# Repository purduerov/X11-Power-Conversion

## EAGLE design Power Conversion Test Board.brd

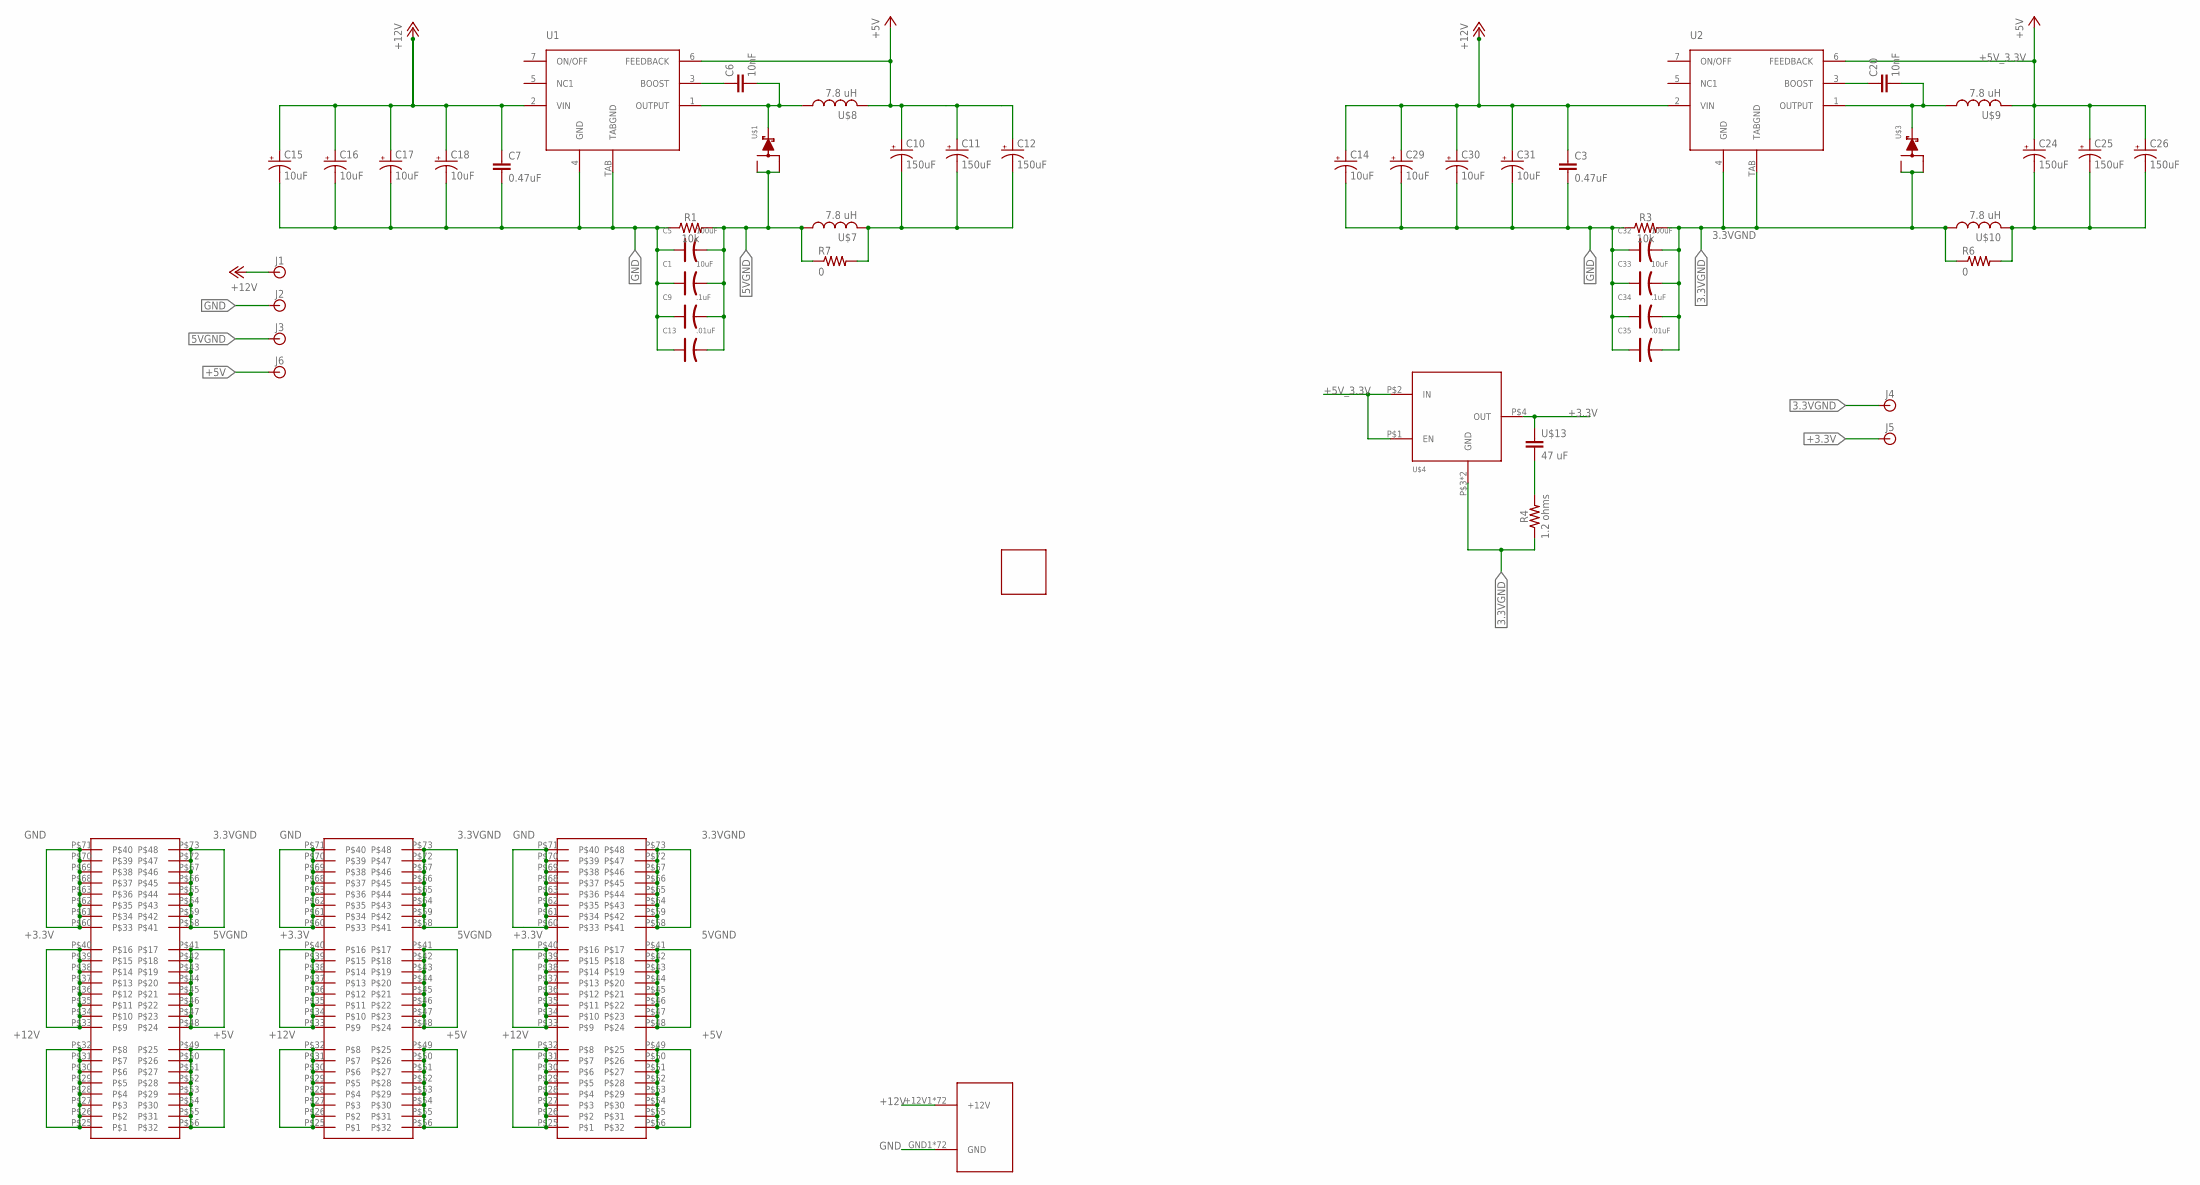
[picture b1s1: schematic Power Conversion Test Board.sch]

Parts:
C1, C33: 10uF; AVX-A
C3, C7: 0.47uF; C0603
C5, C32: 100uF; AVX-A
C6, C20: 10nF; 0603
C9, C34: .1uF; AVX-A
C10, C11, C12, C24, C25, C26: 150uF; CTAN(7.30_4.30MM)
C13, C35: .01uF; AVX-A
C14, C15, C16, C17, C18, C29, C30, C31: 10uF; CTAN(7.30_4.30MM)
J1, J2, J3, J4, J5, J6: BANANA_CONN
R1, R3: 10k; 0603
R4: 1.2 ohms; 0603
R6, R7: 0; R1206
U1, U2: LM2678
U$1, U$3: SWITCHMODE_SCHOTTKY; DPAK-3
U$2: PDB_PCB_CONNEC; PDB_PCB_2
U$4: TO-263
U$5: BOARDPCB; PCB
U$6, U$11, U$12: ET60S
U$7, U$8, U$9, U$10: 7.8 uH; HCMA1305
U$13: 47 uF; RESC0603_N

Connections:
3.3VGND: C32.-, C33.-, C34.-, C35.-, J4.P$1, R3.2, R4.1, R6.1, U2.4 (GND), U2.TAB (TABGND), U$3.P$1, U$3.P$3, U$4.P$3 (GND), U$4.P$6 (GND), U$6.P$58, U$6.P$59, U$6.P$64, U$6.P$65, U$6.P$66, U$6.P$67, U$6.P$72, U$6.P$73, U$10.P$1 (1), U$11.P$58, U$11.P$59, U$11.P$64, U$11.P$65, U$11.P$66, U$11.P$67, U$11.P$72, U$11.P$73, U$12.P$58, U$12.P$59, U$12.P$64, U$12.P$65, U$12.P$66, U$12.P$67, U$12.P$72, U$12.P$73
5VGND: C1.-, C5.-, C9.-, C13.-, J3.P$1, R1.2, R7.1, U$1.P$1, U$1.P$3, U$6.P$41, U$6.P$42, U$6.P$43, U$6.P$44, U$6.P$45, U$6.P$46, U$6.P$47, U$6.P$48, U$7.P$1 (1), U$11.P$41, U$11.P$42, U$11.P$43, U$11.P$44, U$11.P$45, U$11.P$46, U$11.P$47, U$11.P$48, U$12.P$41, U$12.P$42, U$12.P$43, U$12.P$44, U$12.P$45, U$12.P$46, U$12.P$47, U$12.P$48
+3.3V: J5.P$1, U$4.P$4 (OUT), U$6.P$33, U$6.P$34, U$6.P$35, U$6.P$36, U$6.P$37, U$6.P$38, U$6.P$39, U$6.P$40, U$11.P$33, U$11.P$34, U$11.P$35, U$11.P$36, U$11.P$37, U$11.P$38, U$11.P$39, U$11.P$40, U$12.P$33, U$12.P$34, U$12.P$35, U$12.P$36, U$12.P$37, U$12.P$38, U$12.P$39, U$12.P$40, U$13.1
+5V: C10.+, C11.+, C12.+, J6.P$1, U1.6 (FEEDBACK), U$6.P$49, U$6.P$50, U$6.P$51, U$6.P$52, U$6.P$53, U$6.P$54, U$6.P$55, U$6.P$56, U$8.P$2 (2), U$11.P$49, U$11.P$50, U$11.P$51, U$11.P$52, U$11.P$53, U$11.P$54, U$11.P$55, U$11.P$56, U$12.P$49, U$12.P$50, U$12.P$51, U$12.P$52, U$12.P$53, U$12.P$54, U$12.P$55, U$12.P$56
+5V_3.3V: C24.+, C25.+, C26.+, U2.6 (FEEDBACK), U$4.P$1 (EN), U$4.P$2 (IN), U$9.P$2 (2)
+12V: C3.1, C7.1, C14.+, C15.+, C16.+, C17.+, C18.+, C29.+, C30.+, C31.+, J1.P$1, U1.2 (VIN), U2.2 (VIN), U$2.+12V1 (+12V), U$2.+12V2 (+12V), U$2.+12V3 (+12V), U$2.+12V4 (+12V), U$2.+12V5 (+12V), U$2.+12V6 (+12V), U$2.+12V7 (+12V), U$2.+12V8 (+12V), U$2.+12V9 (+12V), U$2.+12V10 (+12V), U$2.+12V11 (+12V), U$2.+12V12 (+12V), U$2.+12V13 (+12V), U$2.+12V14 (+12V), U$2.+12V15 (+12V), U$2.+12V16 (+12V), U$2.+12V17 (+12V), U$2.+12V18 (+12V), U$2.+12V19 (+12V), U$2.+12V20 (+12V), U$2.+12V21 (+12V), U$2.+12V22 (+12V), U$2.+12V23 (+12V), U$2.+12V24 (+12V), U$2.+12V25 (+12V), U$2.+12V26 (+12V), U$2.+12V27 (+12V), U$2.+12V28 (+12V), U$2.+12V29 (+12V), U$2.+12V30 (+12V), U$2.+12V31 (+12V), U$2.+12V32 (+12V), U$2.+12V33 (+12V), U$2.+12V34 (+12V), U$2.+12V35 (+12V), U$2.+12V36 (+12V), U$2.+12V37 (+12V), U$2.+12V38 (+12V), U$2.+12V39 (+12V), U$2.+12V40 (+12V), U$2.+12V41 (+12V), U$2.+12V42 (+12V), U$2.+12V43 (+12V), U$2.+12V44 (+12V), U$2.+12V45 (+12V), U$2.+12V46 (+12V), U$2.+12V47 (+12V), U$2.+12V48 (+12V), U$2.+12V49 (+12V), U$2.+12V50 (+12V), U$2.+12V51 (+12V), U$2.+12V52 (+12V), U$2.+12V53 (+12V), U$2.+12V54 (+12V), U$2.+12V55 (+12V), U$2.+12V56 (+12V), U$2.+12V57 (+12V), U$2.+12V58 (+12V), U$2.+12V59 (+12V), U$2.+12V60 (+12V), U$2.+12V61 (+12V), U$2.+12V62 (+12V), U$2.+12V63 (+12V), U$2.+12V64 (+12V), U$2.+12V65 (+12V), U$2.+12V66 (+12V), U$2.+12V67 (+12V), U$2.+12V68 (+12V), U$2.+12V69 (+12V), U$2.+12V70 (+12V), U$2.+12V71 (+12V), U$2.+12V72 (+12V), U$6.P$25, U$6.P$26, U$6.P$27, U$6.P$28, U$6.P$29, U$6.P$30, U$6.P$31, U$6.P$32, U$11.P$25, U$11.P$26, U$11.P$27, U$11.P$28, U$11.P$29, U$11.P$30, U$11.P$31, U$11.P$32, U$12.P$25, U$12.P$26, U$12.P$27, U$12.P$28, U$12.P$29, U$12.P$30, U$12.P$31, U$12.P$32
GND: C1.+, C3.2, C5.+, C7.2, C9.+, C13.+, C14.-, C15.-, C16.-, C17.-, C18.-, C29.-, C30.-, C31.-, C32.+, C33.+, C34.+, C35.+, J2.P$1, R1.1, R3.1, U1.4 (GND), U1.TAB (TABGND), U$2.GND1 (GND), U$2.GND2 (GND), U$2.GND3 (GND), U$2.GND4 (GND), U$2.GND5 (GND), U$2.GND6 (GND), U$2.GND7 (GND), U$2.GND8 (GND), U$2.GND9 (GND), U$2.GND10 (GND), U$2.GND11 (GND), U$2.GND12 (GND), U$2.GND13 (GND), U$2.GND14 (GND), U$2.GND15 (GND), U$2.GND16 (GND), U$2.GND17 (GND), U$2.GND18 (GND), U$2.GND19 (GND), U$2.GND20 (GND), U$2.GND21 (GND), U$2.GND22 (GND), U$2.GND23 (GND), U$2.GND24 (GND), U$2.GND25 (GND), U$2.GND26 (GND), U$2.GND27 (GND), U$2.GND28 (GND), U$2.GND29 (GND), U$2.GND30 (GND), U$2.GND31 (GND), U$2.GND32 (GND), U$2.GND33 (GND), U$2.GND34 (GND), U$2.GND35 (GND), U$2.GND36 (GND), U$2.GND37 (GND), U$2.GND38 (GND), U$2.GND39 (GND), U$2.GND40 (GND), U$2.GND41 (GND), U$2.GND42 (GND), U$2.GND43 (GND), U$2.GND44 (GND), U$2.GND45 (GND), U$2.GND46 (GND), U$2.GND47 (GND), U$2.GND48 (GND), U$2.GND49 (GND), U$2.GND50 (GND), U$2.GND51 (GND), U$2.GND52 (GND), U$2.GND53 (GND), U$2.GND54 (GND), U$2.GND55 (GND), U$2.GND56 (GND), U$2.GND57 (GND), U$2.GND58 (GND), U$2.GND59 (GND), U$2.GND60 (GND), U$2.GND61 (GND), U$2.GND62 (GND), U$2.GND63 (GND), U$2.GND64 (GND), U$2.GND65 (GND), U$2.GND66 (GND), U$2.GND67 (GND), U$2.GND68 (GND), U$2.GND69 (GND), U$2.GND70 (GND), U$2.GND71 (GND), U$2.GND72 (GND), U$6.P$60, U$6.P$61, U$6.P$62, U$6.P$63, U$6.P$68, U$6.P$69, U$6.P$70, U$6.P$71, U$11.P$60, U$11.P$61, U$11.P$62, U$11.P$63, U$11.P$68, U$11.P$69, U$11.P$70, U$11.P$71, U$12.P$60, U$12.P$61, U$12.P$62, U$12.P$63, U$12.P$68, U$12.P$69, U$12.P$70, U$12.P$71
unnamed: C6.2, U1.1 (OUTPUT), U$1.P$4, U$8.P$1 (1)
unnamed: C20.1, U2.3 (BOOST)
unnamed: C6.1, U1.3 (BOOST)
unnamed: C24.-, C25.-, C26.-, R6.2, U$10.P$2 (2)
unnamed: C20.2, U2.1 (OUTPUT), U$3.P$4, U$9.P$1 (1)
unnamed: C10.-, C11.-, C12.-, R7.2, U$7.P$2 (2)
unnamed: R4.2, U$13.2

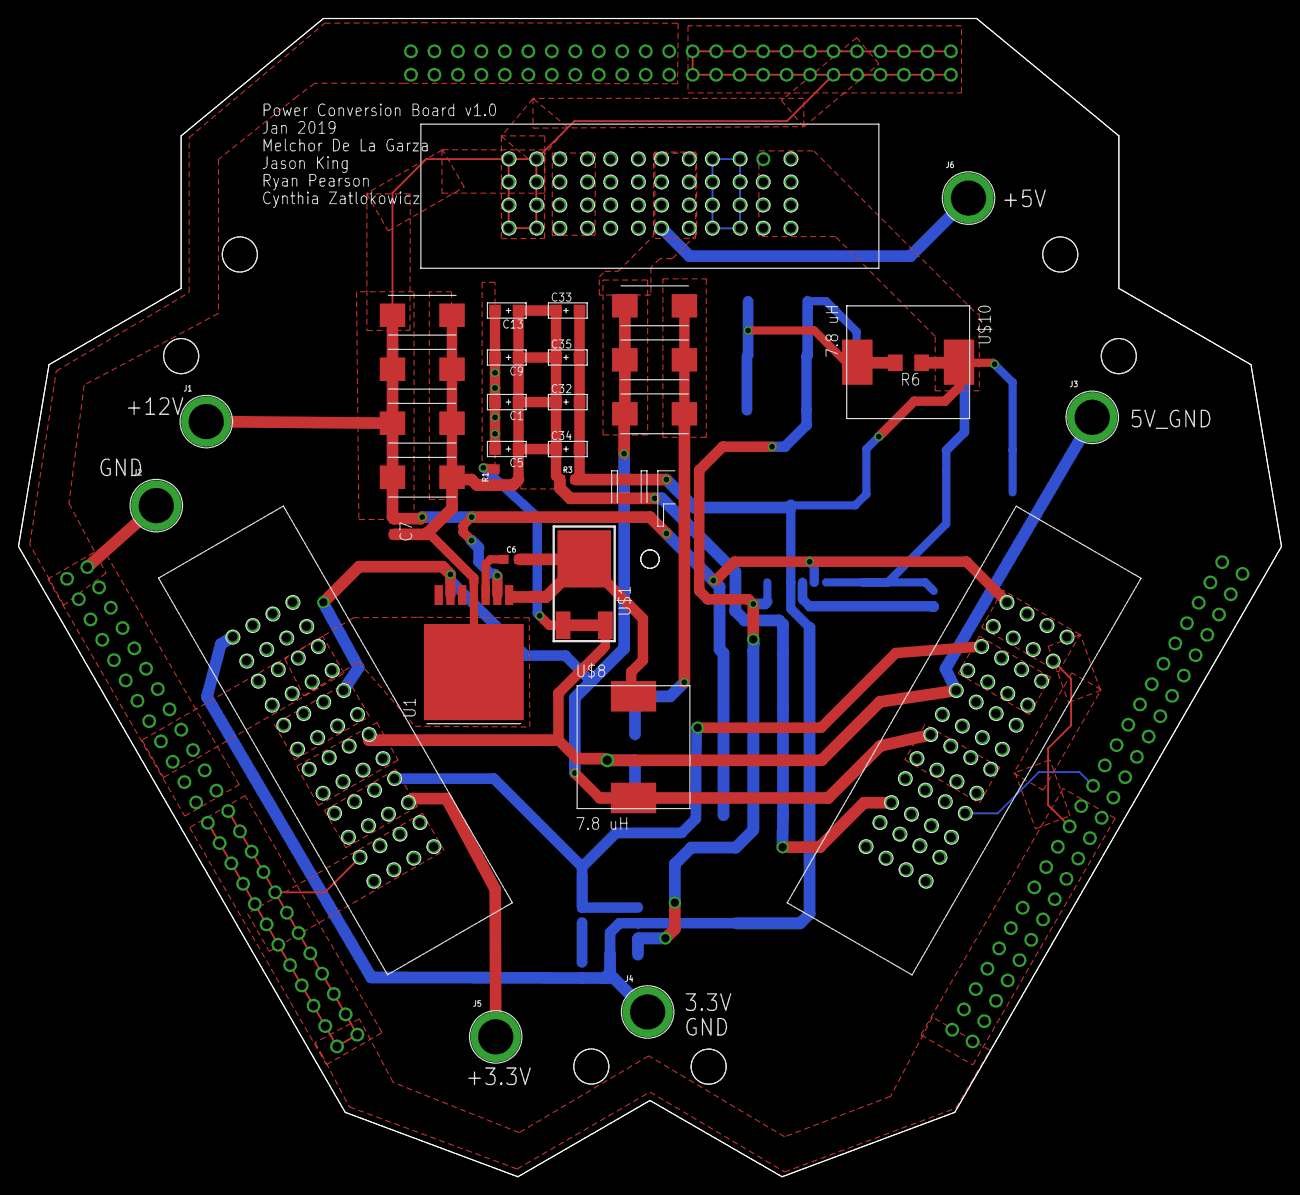
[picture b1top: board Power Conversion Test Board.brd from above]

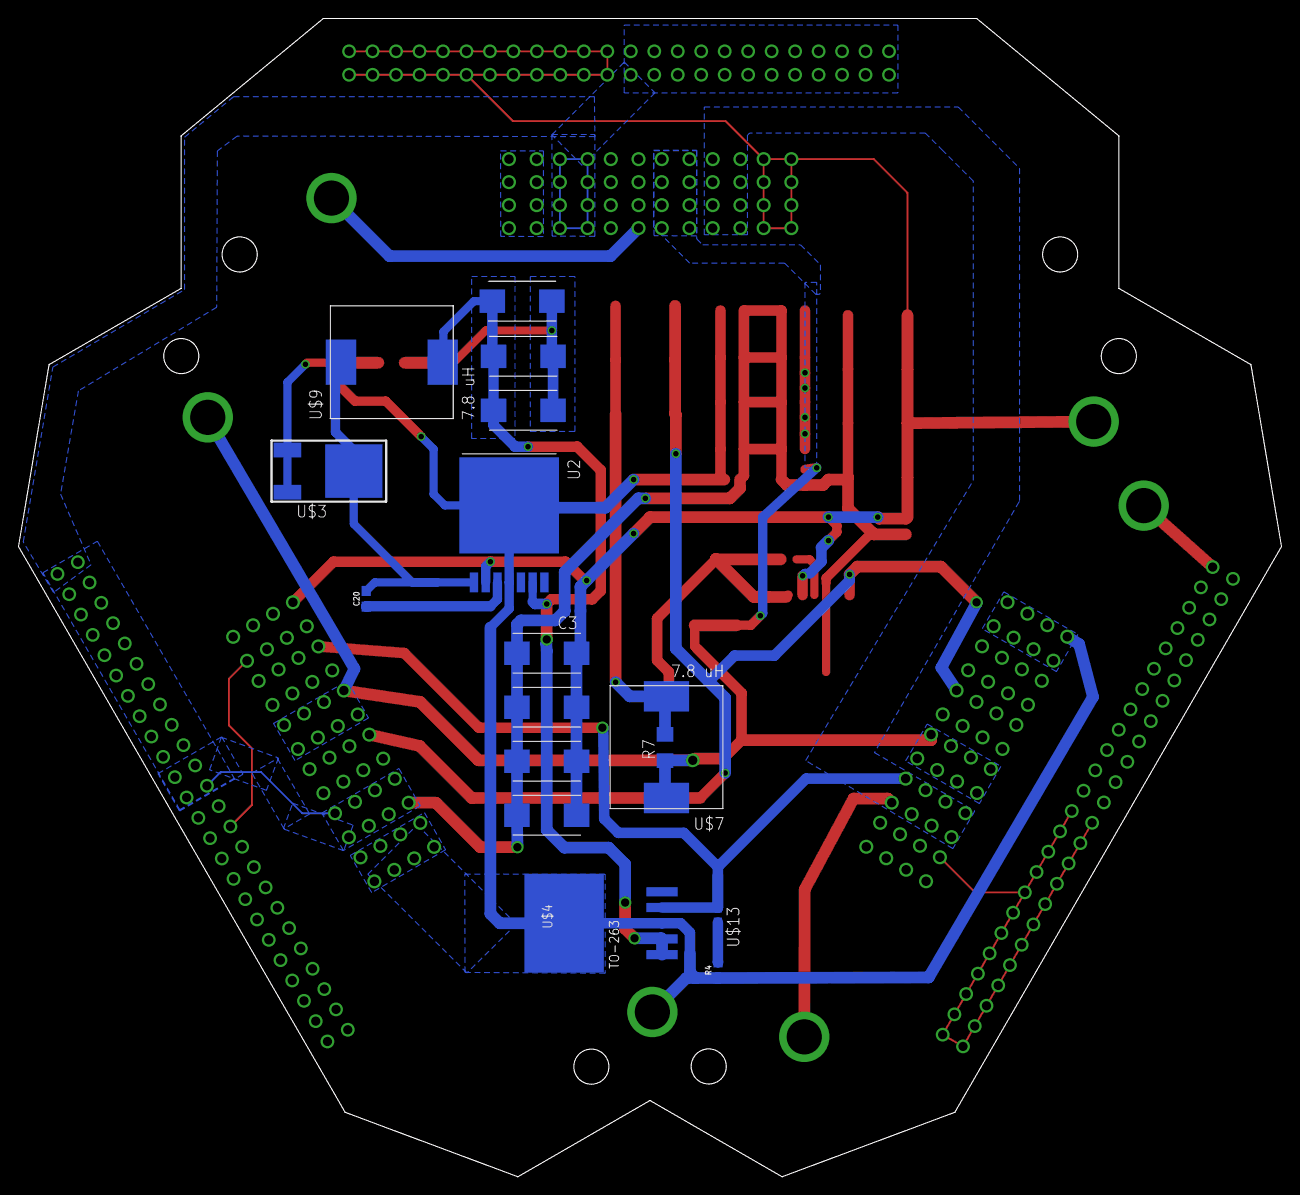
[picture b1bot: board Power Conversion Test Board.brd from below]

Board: 4 copper layers, 136.7 x 125.3 mm, 52 parts (17 on the bottom side), 14 nets.

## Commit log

2018-09-19 added gitignore
2018-10-13 Added 3.3V linear regulator
    added 3.3V linear regulator and corresponding components
2018-10-13 added the right connnections
    fixed up the connections on the 3.3V line
2018-10-13 Changed GND signals so they are different for different circuits
2018-10-13 Added components to allow fixing if it doesnt work with split inductors, @melchor repeat with the 12->5v3 circuit
2018-10-14 Fixed Resistor Value
    Fixed the resistor value on the 3.3 V linear regulator line
2018-10-17 added the resistor and inductor
    added the 0ohm resistor and 15 uH inductor to the other buck
2018-10-18 added the outline
    should go according to this outline, but dont need to for the test board
2018-10-20 lots of things
    put in board outline, also fixed the inductors because they were the wrong ones
2018-10-25 Changed schematic layout and starting routing
2018-10-27 Rerouting
2018-10-29 Repositioned the components of the board to get ready for tracing
2018-10-30 re-positioned parts
2018-10-30 Routed board
    board is routed
2018-11-01 ripped board up and started over
2018-11-01 Updated board positioning
2018-11-03 Replaced components and routed some more.
2018-11-03 the good stuffff
2018-11-09 Added connectors
2018-11-09 moved connectors
2018-11-10 added connectors
    the ones that go to distribution
2018-11-29 moved board to origin
2018-11-30 Did stuff and corrected stuff
2018-11-30 Added the updated ET60S connectors
2018-11-30 fixed a trace
2018-12-13 Changed stuff
2018-12-15 Replaced connectors
    the ones to the distribution board
2018-12-31 Made some minor changes to the board, just uploading for saving purposes
2019-01-01 minor changes
2019-01-02 Netted connectors
2019-01-02 small tweak on connectors
2019-01-02 changes made
2019-01-03 Changed connector voltage locations and other edits
2019-01-04 Updated stuff
2019-01-04 fixed 12VGND to just be GND, connected everything on the connectors
2019-01-11 Minor Edits to Finalize board
2019-01-11 added some text and silkscreen
2019-01-12 added some labels
    labeled the test points for each voltage
2019-01-12 i forgot the date
2019-01-12 fixed silkscreen
    loooks muuy buenoo
2019-01-12 replaced 47 uF capacitor

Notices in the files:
parts and their libraries:
SparkFun-Capacitors: Licensing: Creative Commons ShareAlike 4.0 International - https://creativecommons.org/licenses/by-sa/4.0
